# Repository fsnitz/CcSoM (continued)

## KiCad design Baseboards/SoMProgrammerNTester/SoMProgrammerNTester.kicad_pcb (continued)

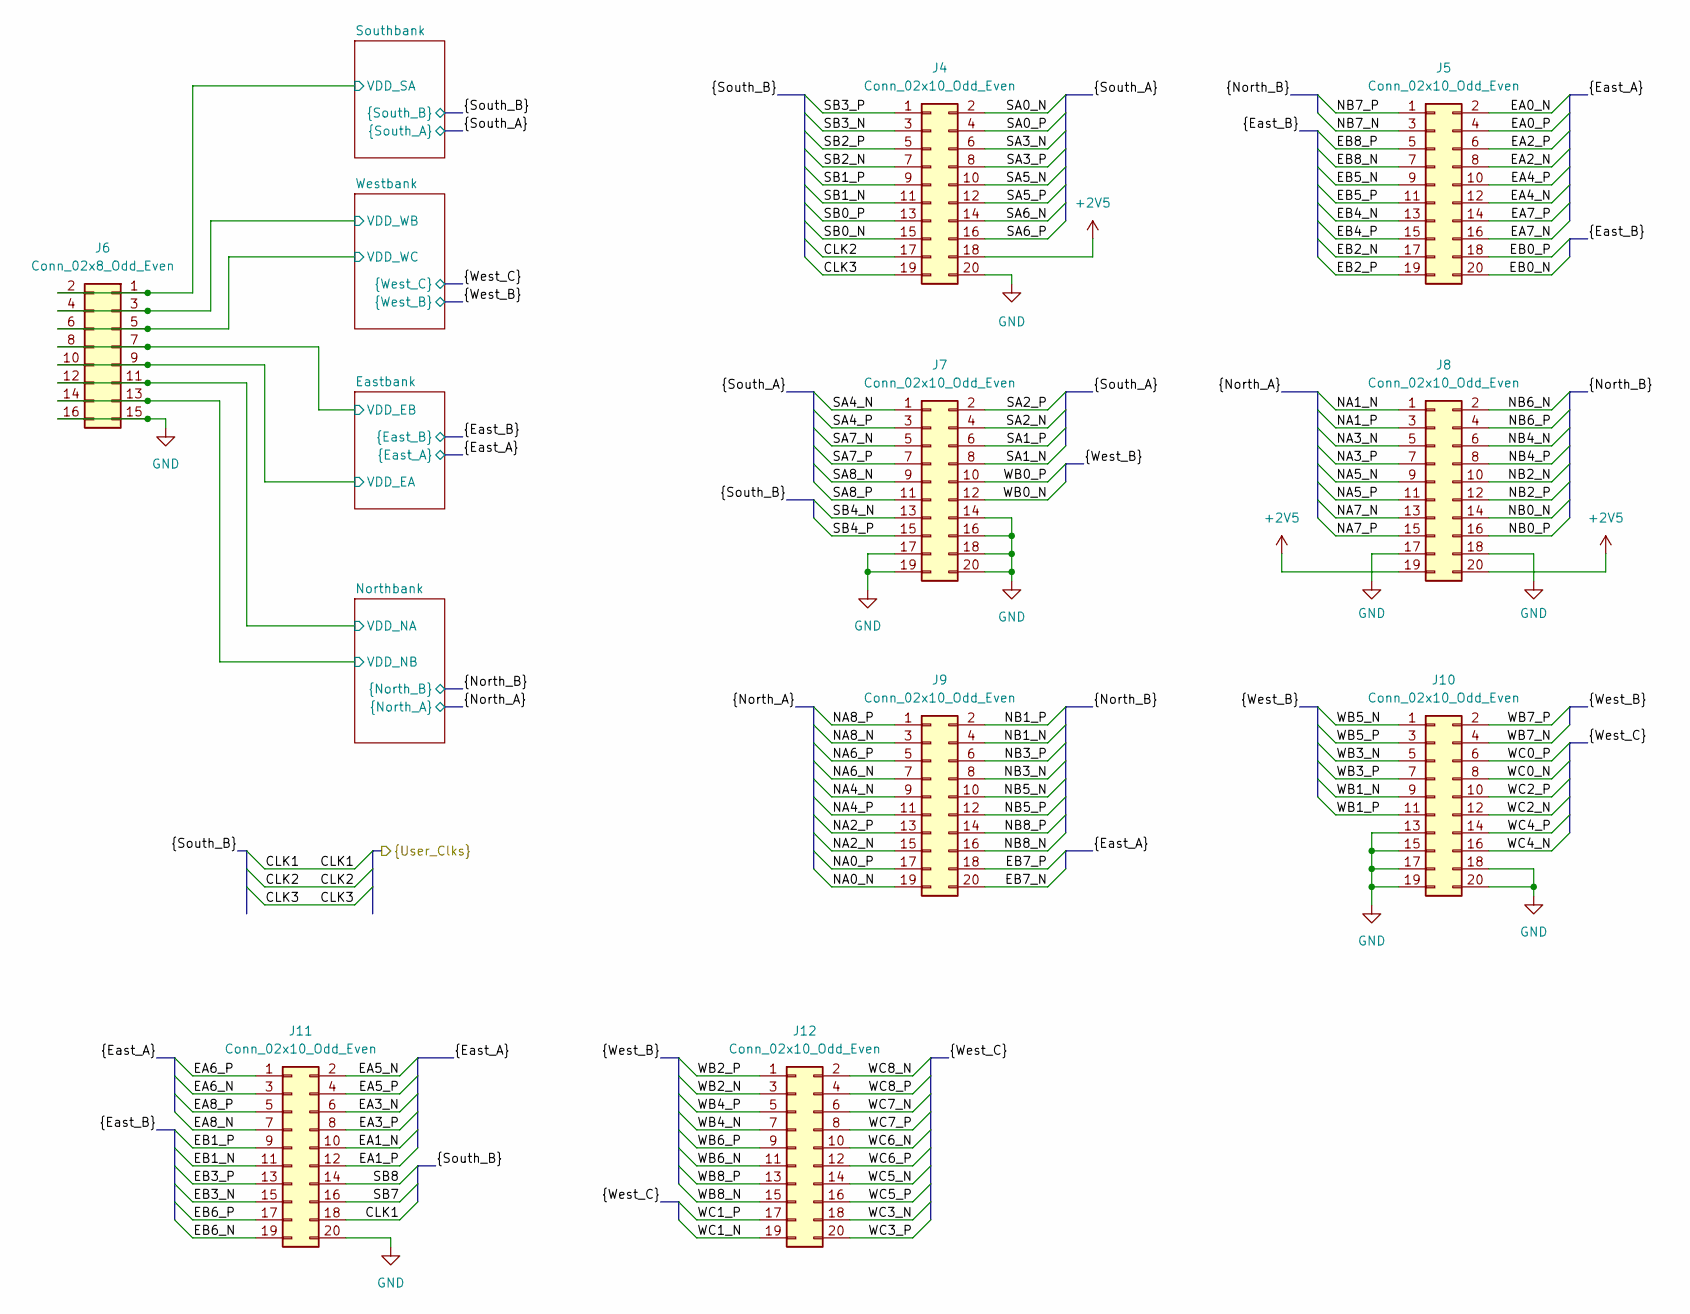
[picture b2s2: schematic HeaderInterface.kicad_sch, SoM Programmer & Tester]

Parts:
J4, J5, J7, J8, J9, J10, J11, J12: Conn_02x10_Odd_Even; PinHeader_2x10_P2.54mm_Vertical; Mouser Part Number 649-1012938192002BLF
J6: Conn_02x8_Odd_Even; PinHeader_2x08_P2.54mm_Vertical; Mouser Part Number 649-1012938191601BLF

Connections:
+2V5: J4.18, J8.19, J8.20; also elsewhere on the board
/CLK1: J11.18; also elsewhere on the board
/CLK2: J4.17; also elsewhere on the board
/CLK3: J4.19; also elsewhere on the board
/Header Interface/EA0_N: J5.2; also elsewhere on the board
/Header Interface/EA0_P: J5.4; also elsewhere on the board
/Header Interface/EA1_N: J11.10; also elsewhere on the board
/Header Interface/EA1_P: J11.12; also elsewhere on the board
/Header Interface/EA2_N: J5.8; also elsewhere on the board
/Header Interface/EA2_P: J5.6; also elsewhere on the board
/Header Interface/EA3_N: J11.6; also elsewhere on the board
/Header Interface/EA3_P: J11.8; also elsewhere on the board
/Header Interface/EA4_N: J5.12; also elsewhere on the board
/Header Interface/EA4_P: J5.10; also elsewhere on the board
/Header Interface/EA5_N: J11.2; also elsewhere on the board
/Header Interface/EA5_P: J11.4; also elsewhere on the board
/Header Interface/EA6_N: J11.3; also elsewhere on the board
/Header Interface/EA6_P: J11.1; also elsewhere on the board
/Header Interface/EA7_N: J5.16; also elsewhere on the board
/Header Interface/EA7_P: J5.14; also elsewhere on the board
/Header Interface/EA8_N: J11.7; also elsewhere on the board
/Header Interface/EA8_P: J11.5; also elsewhere on the board
/Header Interface/EB0_N: J5.20; also elsewhere on the board
/Header Interface/EB0_P: J5.18; also elsewhere on the board
/Header Interface/EB1_N: J11.11; also elsewhere on the board
/Header Interface/EB1_P: J11.9; also elsewhere on the board
/Header Interface/EB2_N: J5.17; also elsewhere on the board
/Header Interface/EB2_P: J5.19; also elsewhere on the board
/Header Interface/EB3_N: J11.15; also elsewhere on the board
/Header Interface/EB3_P: J11.13; also elsewhere on the board
/Header Interface/EB4_N: J5.13; also elsewhere on the board
/Header Interface/EB4_P: J5.15; also elsewhere on the board
/Header Interface/EB5_N: J5.9; also elsewhere on the board
/Header Interface/EB5_P: J5.11; also elsewhere on the board
/Header Interface/EB6_N: J11.19; also elsewhere on the board
/Header Interface/EB6_P: J11.17; also elsewhere on the board
/Header Interface/EB7_N: J9.20; also elsewhere on the board
/Header Interface/EB7_P: J9.18; also elsewhere on the board
/Header Interface/EB8_N: J5.7; also elsewhere on the board
/Header Interface/EB8_P: J5.5; also elsewhere on the board
/Header Interface/Eastbank/VDD_EA: J6.9, J6.10; also elsewhere on the board
/Header Interface/Eastbank/VDD_EB: J6.7, J6.8; also elsewhere on the board
/Header Interface/NA0_N: J9.19; also elsewhere on the board
/Header Interface/NA0_P: J9.17; also elsewhere on the board
/Header Interface/NA1_N: J8.1; also elsewhere on the board
/Header Interface/NA1_P: J8.3; also elsewhere on the board
/Header Interface/NA2_N: J9.15; also elsewhere on the board
/Header Interface/NA2_P: J9.13; also elsewhere on the board
/Header Interface/NA3_N: J8.5; also elsewhere on the board
/Header Interface/NA3_P: J8.7; also elsewhere on the board
/Header Interface/NA4_N: J9.9; also elsewhere on the board
/Header Interface/NA4_P: J9.11; also elsewhere on the board
/Header Interface/NA5_N: J8.9; also elsewhere on the board
/Header Interface/NA5_P: J8.11; also elsewhere on the board
/Header Interface/NA6_N: J9.7; also elsewhere on the board
/Header Interface/NA6_P: J9.5; also elsewhere on the board
/Header Interface/NA7_N: J8.13; also elsewhere on the board
/Header Interface/NA7_P: J8.15; also elsewhere on the board
/Header Interface/NA8_N: J9.3; also elsewhere on the board
/Header Interface/NA8_P: J9.1; also elsewhere on the board
/Header Interface/NB0_N: J8.14; also elsewhere on the board
/Header Interface/NB0_P: J8.16; also elsewhere on the board
/Header Interface/NB1_N: J9.4; also elsewhere on the board
/Header Interface/NB1_P: J9.2; also elsewhere on the board
/Header Interface/NB2_N: J8.10; also elsewhere on the board
/Header Interface/NB2_P: J8.12; also elsewhere on the board
/Header Interface/NB3_N: J9.8; also elsewhere on the board
/Header Interface/NB3_P: J9.6; also elsewhere on the board
/Header Interface/NB4_N: J8.6; also elsewhere on the board
/Header Interface/NB4_P: J8.8; also elsewhere on the board
/Header Interface/NB5_N: J9.10; also elsewhere on the board
/Header Interface/NB5_P: J9.12; also elsewhere on the board
/Header Interface/NB6_N: J8.2; also elsewhere on the board
/Header Interface/NB6_P: J8.4; also elsewhere on the board
/Header Interface/NB7_N: J5.3; also elsewhere on the board
/Header Interface/NB7_P: J5.1; also elsewhere on the board
/Header Interface/NB8_N: J9.16; also elsewhere on the board
/Header Interface/NB8_P: J9.14; also elsewhere on the board
/Header Interface/Northbank/VDD_NA: J6.11, J6.12; also elsewhere on the board
/Header Interface/Northbank/VDD_NB: J6.13, J6.14; also elsewhere on the board
/Header Interface/SA0_N: J4.2; also elsewhere on the board
/Header Interface/SA0_P: J4.4; also elsewhere on the board
/Header Interface/SA1_N: J7.8; also elsewhere on the board
/Header Interface/SA1_P: J7.6; also elsewhere on the board
/Header Interface/SA2_N: J7.4; also elsewhere on the board
/Header Interface/SA2_P: J7.2; also elsewhere on the board
/Header Interface/SA3_N: J4.6; also elsewhere on the board
/Header Interface/SA3_P: J4.8; also elsewhere on the board
/Header Interface/SA4_N: J7.1; also elsewhere on the board
/Header Interface/SA4_P: J7.3; also elsewhere on the board
/Header Interface/SA5_N: J4.10; also elsewhere on the board
/Header Interface/SA5_P: J4.12; also elsewhere on the board
/Header Interface/SA6_N: J4.14; also elsewhere on the board
/Header Interface/SA6_P: J4.16; also elsewhere on the board
/Header Interface/SA7_N: J7.5; also elsewhere on the board
/Header Interface/SA7_P: J7.7; also elsewhere on the board
/Header Interface/SA8_N: J7.9; also elsewhere on the board
/Header Interface/SA8_P: J7.11; also elsewhere on the board
/Header Interface/SB0_N: J4.15; also elsewhere on the board
/Header Interface/SB0_P: J4.13; also elsewhere on the board
/Header Interface/SB1_N: J4.11; also elsewhere on the board
/Header Interface/SB1_P: J4.9; also elsewhere on the board
/Header Interface/SB2_N: J4.7; also elsewhere on the board
/Header Interface/SB2_P: J4.5; also elsewhere on the board
/Header Interface/SB3_N: J4.3; also elsewhere on the board
/Header Interface/SB3_P: J4.1; also elsewhere on the board
/Header Interface/SB4_N: J7.13; also elsewhere on the board
/Header Interface/SB4_P: J7.15; also elsewhere on the board
/Header Interface/SB7: J11.16; also elsewhere on the board
/Header Interface/SB8: J11.14; also elsewhere on the board
/Header Interface/Southbank/VDD_SA: J6.1, J6.2; also elsewhere on the board
/Header Interface/WB0_N: J7.12; also elsewhere on the board
/Header Interface/WB0_P: J7.10; also elsewhere on the board
/Header Interface/WB1_N: J10.9; also elsewhere on the board
/Header Interface/WB1_P: J10.11; also elsewhere on the board
/Header Interface/WB2_N: J12.3; also elsewhere on the board
/Header Interface/WB2_P: J12.1; also elsewhere on the board
/Header Interface/WB3_N: J10.5; also elsewhere on the board
/Header Interface/WB3_P: J10.7; also elsewhere on the board
/Header Interface/WB4_N: J12.7; also elsewhere on the board
/Header Interface/WB4_P: J12.5; also elsewhere on the board
/Header Interface/WB5_N: J10.1; also elsewhere on the board
/Header Interface/WB5_P: J10.3; also elsewhere on the board
/Header Interface/WB6_N: J12.11; also elsewhere on the board
/Header Interface/WB6_P: J12.9; also elsewhere on the board
/Header Interface/WB7_N: J10.4; also elsewhere on the board
/Header Interface/WB7_P: J10.2; also elsewhere on the board
/Header Interface/WB8_N: J12.15; also elsewhere on the board
/Header Interface/WB8_P: J12.13; also elsewhere on the board
/Header Interface/WC0_N: J10.8; also elsewhere on the board
/Header Interface/WC0_P: J10.6; also elsewhere on the board
/Header Interface/WC1_N: J12.19; also elsewhere on the board
/Header Interface/WC1_P: J12.17; also elsewhere on the board
/Header Interface/WC2_N: J10.12; also elsewhere on the board
/Header Interface/WC2_P: J10.10; also elsewhere on the board
/Header Interface/WC3_N: J12.18; also elsewhere on the board
/Header Interface/WC3_P: J12.20; also elsewhere on the board
/Header Interface/WC4_N: J10.16; also elsewhere on the board
/Header Interface/WC4_P: J10.14; also elsewhere on the board
/Header Interface/WC5_N: J12.14; also elsewhere on the board
/Header Interface/WC5_P: J12.16; also elsewhere on the board
/Header Interface/WC6_N: J12.10; also elsewhere on the board
/Header Interface/WC6_P: J12.12; also elsewhere on the board
/Header Interface/WC7_N: J12.6; also elsewhere on the board
/Header Interface/WC7_P: J12.8; also elsewhere on the board
/Header Interface/WC8_N: J12.2; also elsewhere on the board
/Header Interface/WC8_P: J12.4; also elsewhere on the board
/Header Interface/Westbank/VDD_WB: J6.3, J6.4; also elsewhere on the board
/Header Interface/Westbank/VDD_WC: J6.5, J6.6; also elsewhere on the board
GND: J4.20, J6.15, J6.16, J7.14, J7.16, J7.17, J7.18, J7.19, J7.20, J8.17, J8.18, J10.13, J10.15, J10.17, J10.18, J10.19, J10.20, J11.20; also elsewhere on the board

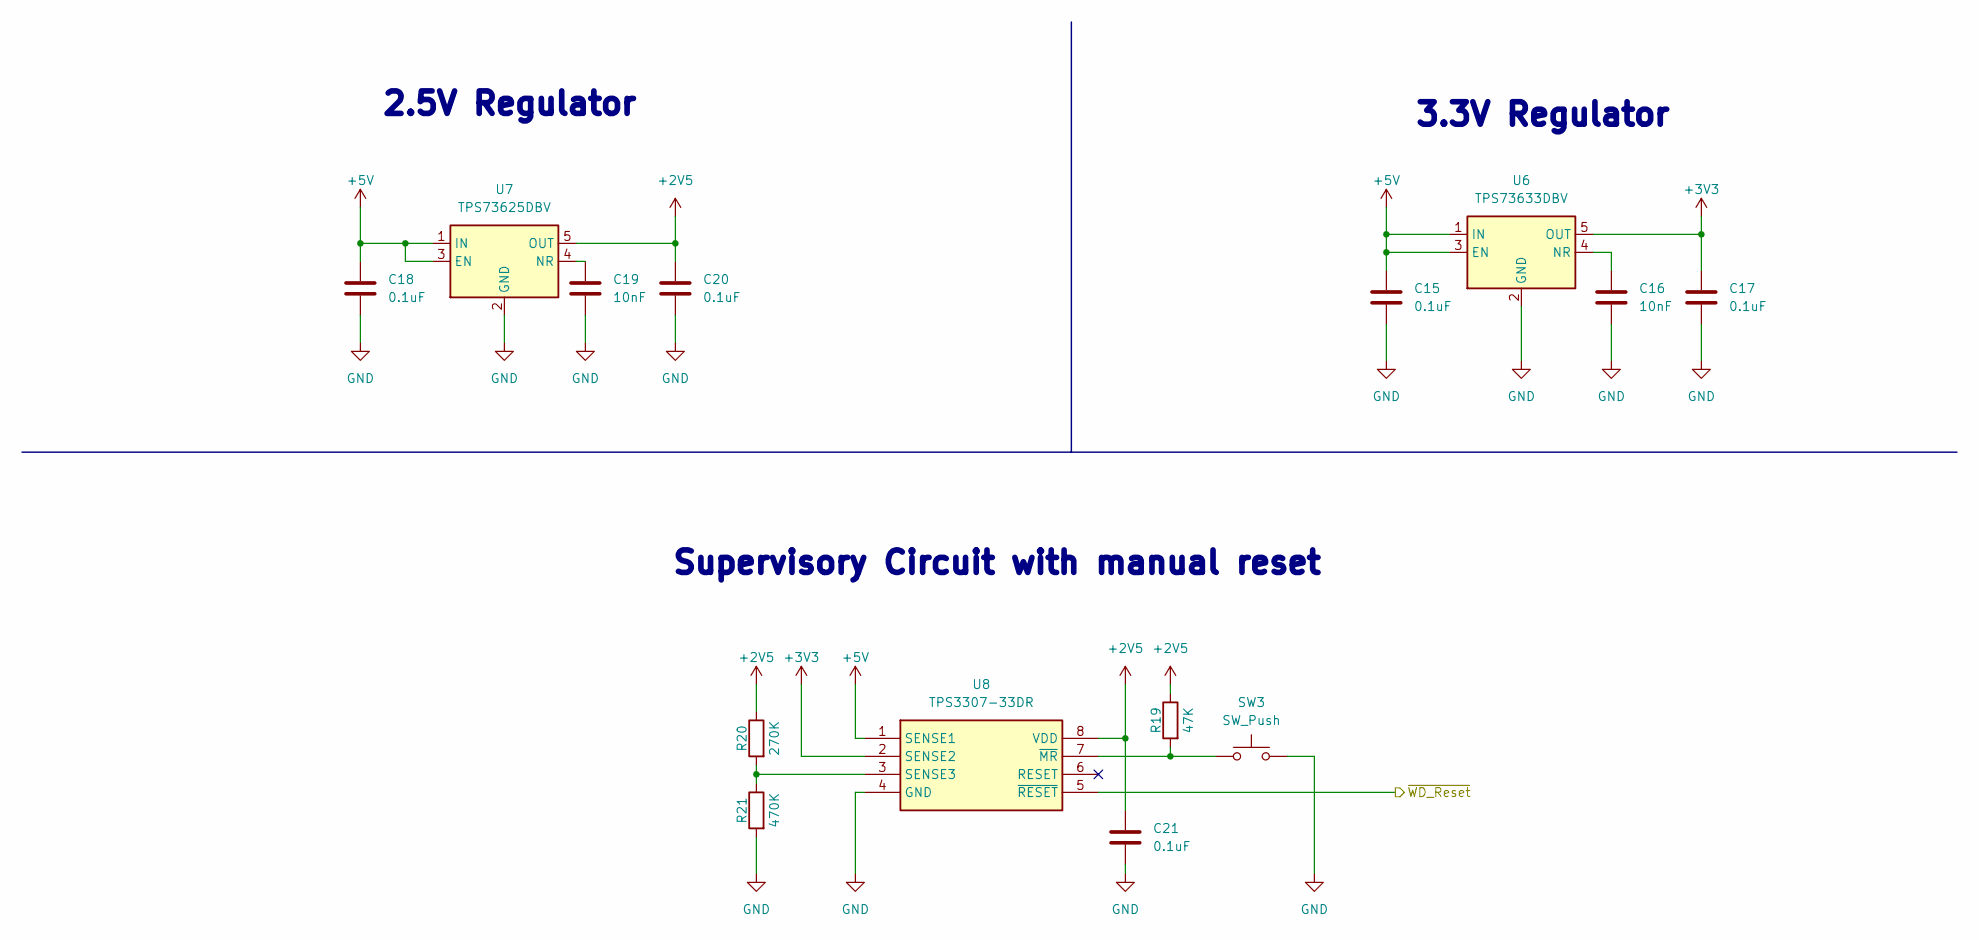
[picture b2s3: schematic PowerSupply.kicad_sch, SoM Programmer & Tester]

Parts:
C15, C17, C18, C20, C21: 0.1uF; C_0603_1608Metric; Mouser Part Number 80-C0603C104M4R7411
C16, C19: 10nF; C_0603_1608Metric; Mouser Part Number 80-C0603X103J4HAUTO
R19: 47K; R_0603_1608Metric; Mouser Part Number 71-CRCW060347K0FKED
R20: 270K; R_0603_1608Metric; Mouser Part Number 71-CRCW0603-270K-E3
R21: 470K; R_0603_1608Metric; Mouser Part Number 71-CRCW0603470KFKEAH
SW3: SW_Push; SW_SPST_TL3305A; Mouser Part Number 612-TL3305AF260QG
U6: TPS73633DBV; SOT-23-5; Mouser Part Number 595-TPS73633DBVRG4
U7: TPS73625DBV; SOT-23-5; Mouser Part Number 595-TPS73625DBVT
U8: TPS3307-33DR; SOIC-8_5.8x3.81mm; Mouser Part Number 595-TPS3307-33DR

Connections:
+2V5: C20.1, C21.1, R19.1, R20.1, U7.5 (OUT), U8.8 (VDD); also elsewhere on the board
+3V3: C17.1, U6.5 (OUT), U8.2 (SENSE2); also elsewhere on the board
+5V: C15.1, C18.1, U6.1 (IN), U6.3 (EN), U7.1 (IN), U7.3 (EN), U8.1 (SENSE1); also elsewhere on the board
/Power supply/~WD_Reset: U8.5 (~RESET); also elsewhere on the board
GND: C15.2, C16.2, C17.2, C18.2, C19.2, C20.2, C21.2, R21.2, SW3.2, U6.2 (GND), U7.2 (GND), U8.4 (GND); also elsewhere on the board
unnamed: C16.1, U6.4 (NR)
unnamed: C19.1, U7.4 (NR)
unnamed: R20.2, R21.1, U8.3 (SENSE3)
unnamed: R19.2, SW3.1, U8.7 (~MR)

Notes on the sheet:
Supervisory Circuit with manual reset
3.3V Regulator
2.5V Regulator

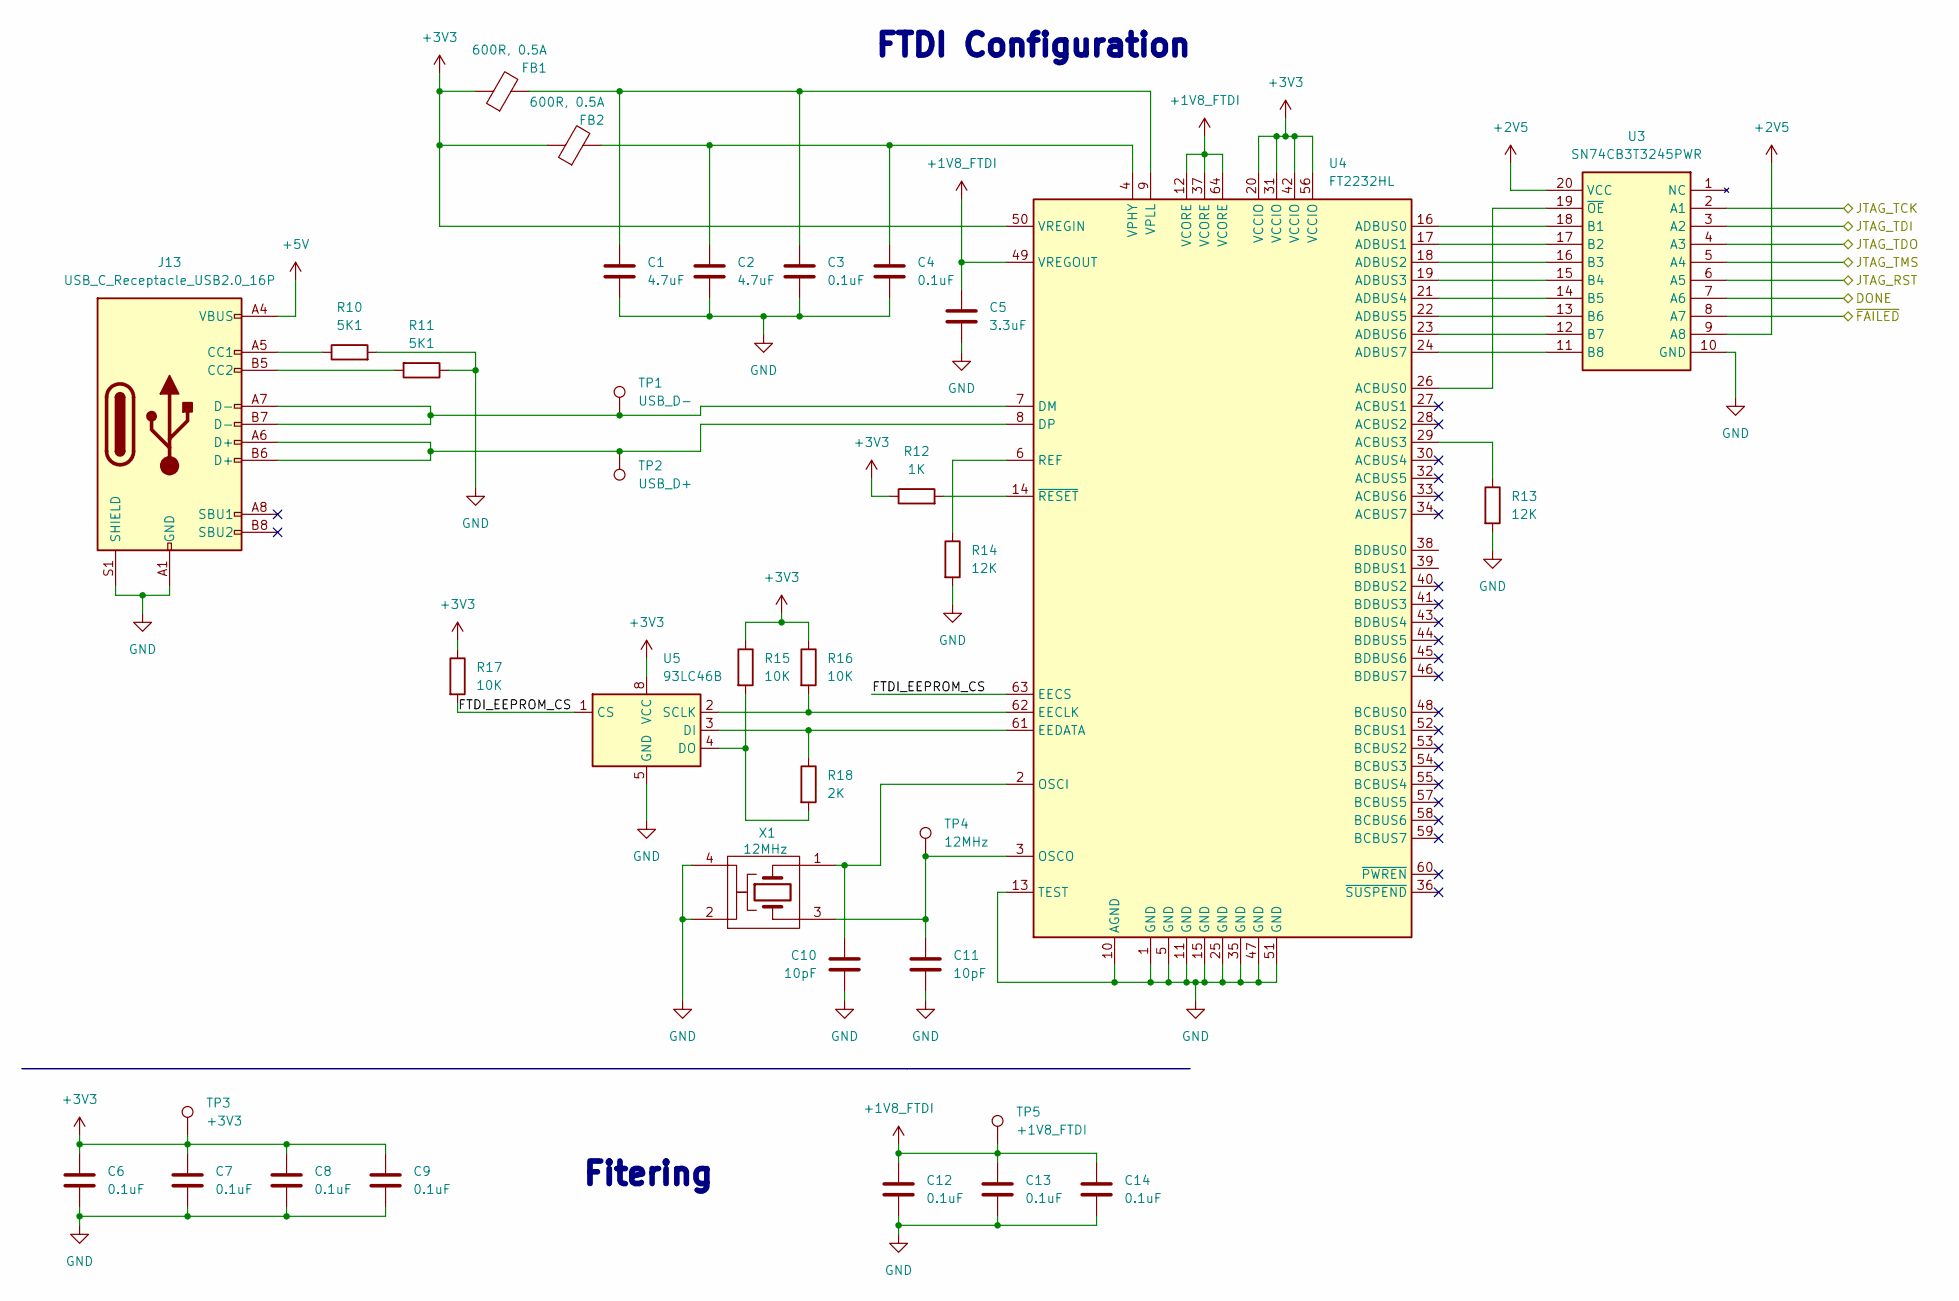
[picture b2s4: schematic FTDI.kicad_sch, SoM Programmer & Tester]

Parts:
C1, C2: 4.7uF; C_0603_1608Metric; Mouser Part Number 963-MSASE168AB5475KT
C3, C4, C6, C7, C8, C9, C12, C13, C14: 0.1uF; C_0603_1608Metric; Mouser Part Number 80-C0603C104M4R7411
C5: 3.3uF; C_0603_1608Metric; Mouser Part Number 810-C1608X5R1C335KAC
C10, C11: 10pF; C_0603_1608Metric; Mouser Part Number 581-0603YA100JAT2A
FB1, FB2: 600R, 0.5A; L_0603_1608Metric; Mouser Part Number 810-MMZ1608R601ATD25
J13: USB_C_Receptacle_USB2.0_16P; USB_C_Receptacle_GCT_USB4110; Mouser Part Number 640-USB4110-GF-A
R10, R11: 5K1; R_0603_1608Metric; Mouser Part Number 71-RCS060356K0FKEA
R12: 1K; R_0603_1608Metric; Mouser Part Number 71-CRCW0603-1.0K-E3
R13, R14: 12K; R_0603_1608Metric; Mouser Part Number 71-CRCW0603-12K-E3
R15, R16, R17: 10K; R_0603_1608Metric; Mouser Part Number 71-CRCW060310K0FKED
R18: 2K; R_0603_1608Metric; Mouser Part Number 71-TNPW06032K00FHEA
TP1: USB_D-; TestPoint_Pad_D1.5mm
TP2: USB_D+; TestPoint_Pad_D1.5mm
TP3: +3V3; TestPoint_Pad_D1.5mm
TP4: 12MHz; TestPoint_Pad_D1.5mm
TP5: +1V8_FTDI; TestPoint_Pad_D1.5mm
U3: SN74CB3T3245PWR; TSSOP-20_4.4x6.5mm_P0.65mm; Mouser Part Number 595-SN74CB3T3245PWR
U4: FT2232HL; LQFP-64_10x10mm_P0.5mm; Mouser Part Number 895-FT2232HL
U5: 93LC46B; TSSOP-8_4.4x3mm_P0.65mm; Mouser Part Number 579-93LC46BT-E/ST
X1: 12MHz; Crystal_SMD_Abracon_ABM3B-4Pin_5.0x3.2mm; Mouser Part Number 815-ABM3B-12-T

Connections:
+1V8_FTDI: C5.1, C12.1, C13.1, C14.1, TP5.1, U4.12 (VCORE), U4.37 (VCORE), U4.49 (VREGOUT), U4.64 (VCORE)
+2V5: U3.9 (A8), U3.20 (VCC); also elsewhere on the board
+3V3: C6.1, C7.1, C8.1, C9.1, FB1.1, FB2.1, R12.1, R15.1, R16.1, R17.1, TP3.1, U4.20 (VCCIO), U4.31 (VCCIO), U4.42 (VCCIO), U4.50 (VREGIN), U4.56 (VCCIO), U5.8 (VCC); also elsewhere on the board
+5V: J13.A4 (VBUS), J13.A9 (VBUS), J13.B4 (VBUS), J13.B9 (VBUS); also elsewhere on the board
/DONE: U3.7 (A6); also elsewhere on the board
/FTDI/FTDI_EEPROM_CS: R17.2, U4.63 (EECS), U5.1 (CS)
/FTDI/JTAG_RST: U3.6 (A5); also elsewhere on the board
/FTDI/JTAG_TCK: U3.2 (A1); also elsewhere on the board
/FTDI/JTAG_TDI: U3.3 (A2); also elsewhere on the board
/FTDI/JTAG_TDO: U3.4 (A3); also elsewhere on the board
/FTDI/JTAG_TMS: U3.5 (A4); also elsewhere on the board
/~FAILED: U3.8 (A7); also elsewhere on the board
GND: C1.2, C2.2, C3.2, C4.2, C5.2, C6.2, C7.2, C8.2, C9.2, C10.2, C11.2, C12.2, C13.2, C14.2, J13.A1 (GND), J13.A12 (GND), J13.B1 (GND), J13.B12 (GND), J13.S1 (SHIELD), R10.2, R11.1, R13.2, R14.2, U3.10 (GND), U4.1 (GND), U4.5 (GND), U4.10 (AGND), U4.11 (GND), U4.13 (TEST), U4.15 (GND), U4.25 (GND), U4.35 (GND), U4.47 (GND), U4.51 (GND), U5.5 (GND), X1.2, X1.4; also elsewhere on the board
unnamed: J13.A5 (CC1), R10.1
unnamed: J13.B5 (CC2), R11.2
unnamed: U3.18 (B1), U4.16 (ADBUS0)
unnamed: U3.17 (B2), U4.17 (ADBUS1)
unnamed: U3.16 (B3), U4.18 (ADBUS2)
unnamed: U3.15 (B4), U4.19 (ADBUS3)
unnamed: U3.14 (B5), U4.21 (ADBUS4)
unnamed: U3.13 (B6), U4.22 (ADBUS5)
unnamed: U3.12 (B7), U4.23 (ADBUS6)
unnamed: U3.11 (B8), U4.24 (ADBUS7)
unnamed: U3.19 (~OE), U4.26 (ACBUS0)
unnamed: R13.1, U4.29 (ACBUS3)
unnamed: J13.A7 (D-), J13.B7 (D-), TP1.1, U4.7 (DM)
unnamed: J13.A6 (D+), J13.B6 (D+), TP2.1, U4.8 (DP)
unnamed: R16.2, U4.62 (EECLK), U5.2 (SCLK)
unnamed: R18.1, U4.61 (EEDATA), U5.3 (DI)
unnamed: C10.1, U4.2 (OSCI), X1.1
unnamed: C11.1, TP4.1, U4.3 (OSCO), X1.3
unnamed: R14.1, U4.6 (REF)
unnamed: C2.1, C4.1, FB2.2, U4.4 (VPHY)
unnamed: C1.1, C3.1, FB1.2, U4.9 (VPLL)
unnamed: R12.2, U4.14 (~RESET)
unnamed: R15.2, R18.2, U5.4 (DO)

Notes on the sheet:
Fitering
FTDI Configuration

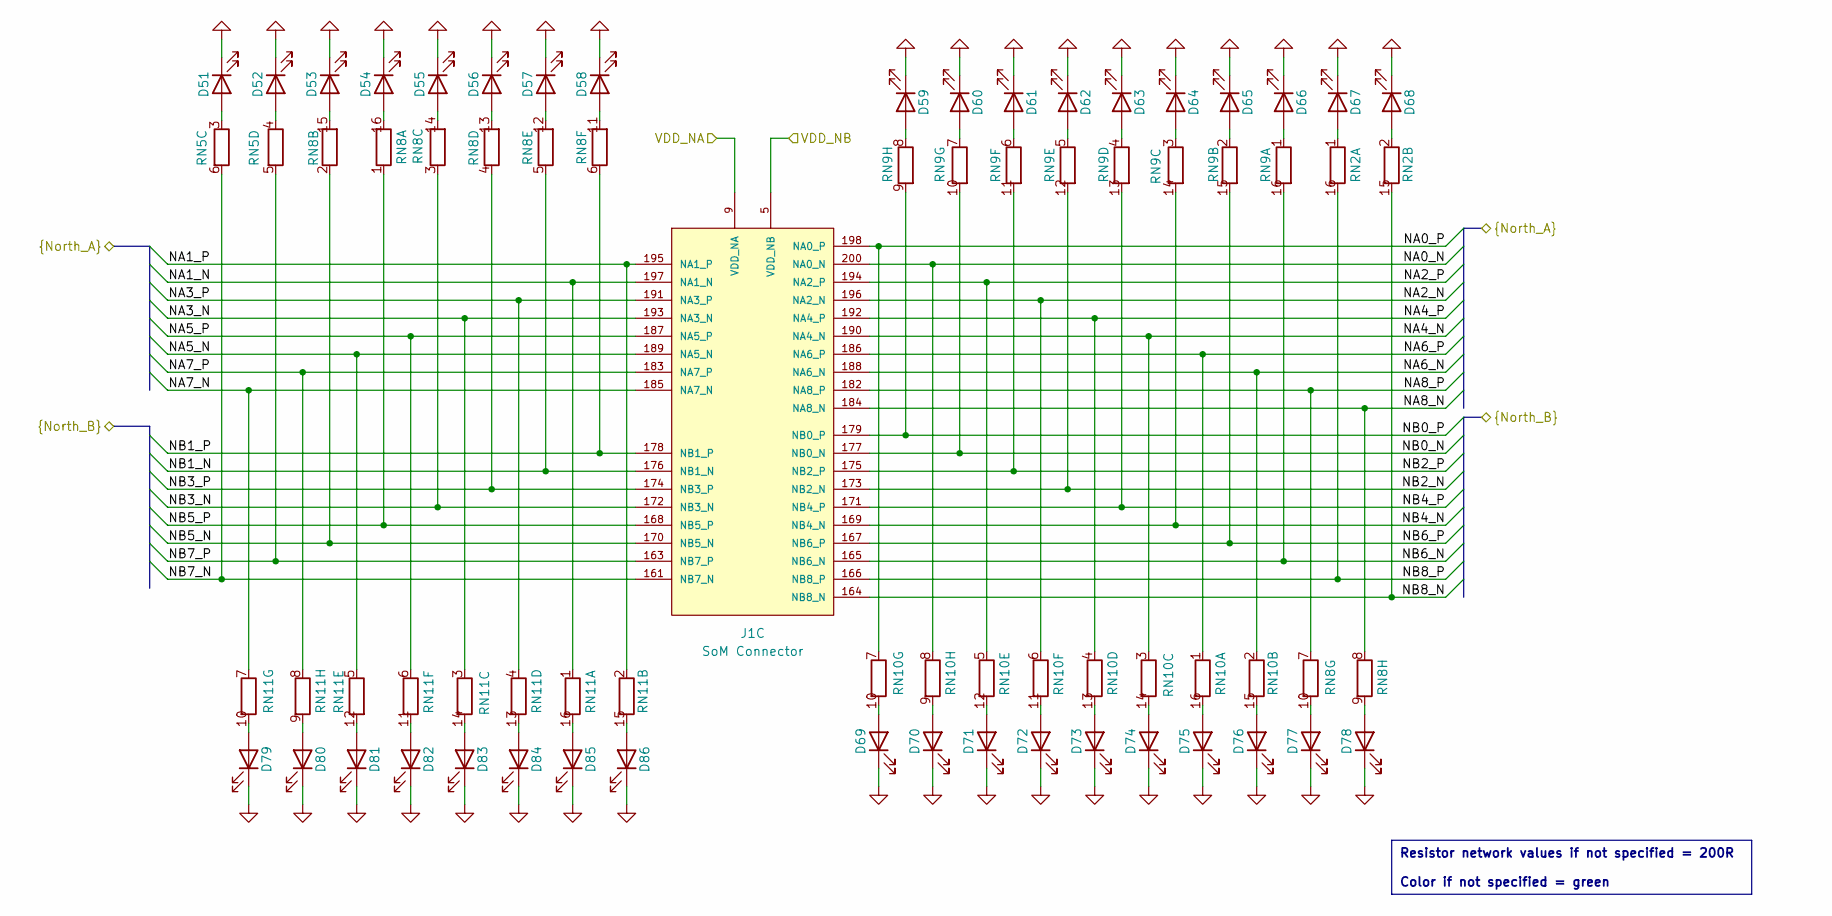
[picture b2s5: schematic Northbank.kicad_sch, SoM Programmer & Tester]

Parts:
D51, D52, D53, D54, D55, D56, D57, D58, D59, D60, D61, D62, D63, D64, D65, D66, D67, D68, D69, D70, D71, D72, D73, D74, D75, D76, D77, D78, D79, D80, D81, D82, D83, D84, D85, D86: Green; LED_0603_1608Metric; Mouser Part Number 710-150060VS75000
J1: SoM Connector; SoM_Connector; Mouser Part Number 571-1473005-1
RN2, RN8, RN9, RN10, RN11: 200R; R_Array_Convex_8x0602; Mouser Part Number 667-EXB-2HV201JV
RN5: 200R; R_Array_Convex_4x0603; Mouser Part Number 667-EXB-38V201JV

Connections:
/Header Interface/NA0_N: J1.200 (NA0_N), RN10.8 (R8.1); also elsewhere on the board
/Header Interface/NA0_P: J1.198 (NA0_P), RN10.7 (R7.1); also elsewhere on the board
/Header Interface/NA1_N: J1.197 (NA1_N), RN11.1 (R1.1); also elsewhere on the board
/Header Interface/NA1_P: J1.195 (NA1_P), RN11.2 (R2.1); also elsewhere on the board
/Header Interface/NA2_N: J1.196 (NA2_N), RN10.6 (R6.1); also elsewhere on the board
/Header Interface/NA2_P: J1.194 (NA2_P), RN10.5 (R5.1); also elsewhere on the board
/Header Interface/NA3_N: J1.193 (NA3_N), RN11.3 (R3.1); also elsewhere on the board
/Header Interface/NA3_P: J1.191 (NA3_P), RN11.4 (R4.1); also elsewhere on the board
/Header Interface/NA4_N: J1.190 (NA4_N), RN10.3 (R3.1); also elsewhere on the board
/Header Interface/NA4_P: J1.192 (NA4_P), RN10.4 (R4.1); also elsewhere on the board
/Header Interface/NA5_N: J1.189 (NA5_N), RN11.5 (R5.1); also elsewhere on the board
/Header Interface/NA5_P: J1.187 (NA5_P), RN11.6 (R6.1); also elsewhere on the board
/Header Interface/NA6_N: J1.188 (NA6_N), RN10.2 (R2.1); also elsewhere on the board
/Header Interface/NA6_P: J1.186 (NA6_P), RN10.1 (R1.1); also elsewhere on the board
/Header Interface/NA7_N: J1.185 (NA7_N), RN11.7 (R7.1); also elsewhere on the board
/Header Interface/NA7_P: J1.183 (NA7_P), RN11.8 (R8.1); also elsewhere on the board
/Header Interface/NA8_N: J1.184 (NA8_N), RN8.8 (R8.1); also elsewhere on the board
/Header Interface/NA8_P: J1.182 (NA8_P), RN8.7 (R7.1); also elsewhere on the board
/Header Interface/NB0_N: J1.177 (NB0_N), RN9.10 (R7.2); also elsewhere on the board
/Header Interface/NB0_P: J1.179 (NB0_P), RN9.9 (R8.2); also elsewhere on the board
/Header Interface/NB1_N: J1.176 (NB1_N), RN8.5 (R5.1); also elsewhere on the board
/Header Interface/NB1_P: J1.178 (NB1_P), RN8.6 (R6.1); also elsewhere on the board
/Header Interface/NB2_N: J1.173 (NB2_N), RN9.12 (R5.2); also elsewhere on the board
/Header Interface/NB2_P: J1.175 (NB2_P), RN9.11 (R6.2); also elsewhere on the board
/Header Interface/NB3_N: J1.172 (NB3_N), RN8.3 (R3.1); also elsewhere on the board
/Header Interface/NB3_P: J1.174 (NB3_P), RN8.4 (R4.1); also elsewhere on the board
/Header Interface/NB4_N: J1.169 (NB4_N), RN9.14 (R3.2); also elsewhere on the board
/Header Interface/NB4_P: J1.171 (NB4_P), RN9.13 (R4.2); also elsewhere on the board
/Header Interface/NB5_N: J1.170 (NB5_N), RN8.2 (R2.1); also elsewhere on the board
/Header Interface/NB5_P: J1.168 (NB5_P), RN8.1 (R1.1); also elsewhere on the board
/Header Interface/NB6_N: J1.165 (NB6_N), RN9.16 (R1.2); also elsewhere on the board
/Header Interface/NB6_P: J1.167 (NB6_P), RN9.15 (R2.2); also elsewhere on the board
/Header Interface/NB7_N: J1.161 (NB7_N), RN5.6 (R3.2); also elsewhere on the board
/Header Interface/NB7_P: J1.163 (NB7_P), RN5.5 (R4.2); also elsewhere on the board
/Header Interface/NB8_N: J1.164 (NB8_N), RN2.15 (R2.2); also elsewhere on the board
/Header Interface/NB8_P: J1.166 (NB8_P), RN2.16 (R1.2); also elsewhere on the board
/Header Interface/Northbank/VDD_NA: J1.9 (VDD_NA); also elsewhere on the board
/Header Interface/Northbank/VDD_NB: J1.5 (VDD_NB); also elsewhere on the board
GND: D51.1 (K), D52.1 (K), D53.1 (K), D54.1 (K), D55.1 (K), D56.1 (K), D57.1 (K), D58.1 (K), D59.1 (K), D60.1 (K), D61.1 (K), D62.1 (K), D63.1 (K), D64.1 (K), D65.1 (K), D66.1 (K), D67.1 (K), D68.1 (K), D69.1 (K), D70.1 (K), D71.1 (K), D72.1 (K), D73.1 (K), D74.1 (K), D75.1 (K), D76.1 (K), D77.1 (K), D78.1 (K), D79.1 (K), D80.1 (K), D81.1 (K), D82.1 (K), D83.1 (K), D84.1 (K), D85.1 (K), D86.1 (K); also elsewhere on the board
unnamed: D51.2 (A), RN5.3 (R3.1)
unnamed: D52.2 (A), RN5.4 (R4.1)
unnamed: D53.2 (A), RN8.15 (R2.2)
unnamed: D54.2 (A), RN8.16 (R1.2)
unnamed: D55.2 (A), RN8.14 (R3.2)
unnamed: D56.2 (A), RN8.13 (R4.2)
unnamed: D57.2 (A), RN8.12 (R5.2)
unnamed: D58.2 (A), RN8.11 (R6.2)
unnamed: D59.2 (A), RN9.8 (R8.1)
unnamed: D60.2 (A), RN9.7 (R7.1)
unnamed: D61.2 (A), RN9.6 (R6.1)
unnamed: D62.2 (A), RN9.5 (R5.1)
unnamed: D63.2 (A), RN9.4 (R4.1)
unnamed: D64.2 (A), RN9.3 (R3.1)
unnamed: D65.2 (A), RN9.2 (R2.1)
unnamed: D66.2 (A), RN9.1 (R1.1)
unnamed: D67.2 (A), RN2.1 (R1.1)
unnamed: D68.2 (A), RN2.2 (R2.1)
unnamed: D69.2 (A), RN10.10 (R7.2)
unnamed: D70.2 (A), RN10.9 (R8.2)
unnamed: D71.2 (A), RN10.12 (R5.2)
unnamed: D72.2 (A), RN10.11 (R6.2)
unnamed: D73.2 (A), RN10.13 (R4.2)
unnamed: D74.2 (A), RN10.14 (R3.2)
unnamed: D75.2 (A), RN10.16 (R1.2)
unnamed: D76.2 (A), RN10.15 (R2.2)
unnamed: D77.2 (A), RN8.10 (R7.2)
unnamed: D78.2 (A), RN8.9 (R8.2)
unnamed: D79.2 (A), RN11.10 (R7.2)
unnamed: D80.2 (A), RN11.9 (R8.2)
unnamed: D81.2 (A), RN11.12 (R5.2)
unnamed: D82.2 (A), RN11.11 (R6.2)
unnamed: D83.2 (A), RN11.14 (R3.2)
unnamed: D84.2 (A), RN11.13 (R4.2)
unnamed: D85.2 (A), RN11.16 (R1.2)
unnamed: D86.2 (A), RN11.15 (R2.2)

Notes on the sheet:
Resistor network values if not specified = 200R Color if not specified = green
